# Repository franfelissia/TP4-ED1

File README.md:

# TP4-ED1

Este proyecto contiene el código y los esquemas del trabajo práctico número 4 de Electrónica Digital 1 de la Facultad de Ciencias Exactas, Físicas y Naturales de la Univercidad Nacional de Córdoba hecho por el grupo 15.

## Consigna

Diseñar y construir en protoboard un Conversor de señal analogica a valores digitales (ADC) que realice la conversión de el valor de tensión proveniente de un divisor resistivo variable (potenciómetro) a 8 bits de salida. Los valores para convertir deben ser de 0 a 5 volt, y se supone que tendrán una frecuencia máxima de 2 KHz.

El trabajo consta de tres partes:

1) Adquisición: Realizar la conversión de la señal analógica y mostrar los valores digitales mediante la utilización de leds que muestren si los bits de salida son cero o uno. Para ello se debe seleccionar una de las siguientes 2 opciones:

    - Utilizar un ADC de aproximaciones sucesivas por ejemplo un ADC0808 o ADC0809.
    - Utilizar ADC de la Basys 3 (FPGA)

2) Almacenamiento: Guardar los valores adquiridos en una memoria RAM de 8 bits. Se deberá poder guardar al menos 5 segundos de muestras de la señal de entrada. Posteriormente, se deberá poder ver en los leds los valores almacenados en la memoria.
 
3) Conversión nuevamente a señal análoga (DAC): Convertir los valores digitales a analógico nuevamente, mediante la utilización de un DAC R-2R.
 
Importante:
Para evitar conflictos en el bus de 8 bits que conectará el ADC y la memoria (ambos intentarán controlar el bus), utilizar las salidas alta impedancia de ambos chips. Un switch decidirá si lo que se muestra en los LEDs o en el DAC viene del ADC o de la memoria.

Recomendación: Utilice en la entrada un generador de señales (pañol), seleccione que emita una señal sinusoidal, y vea la salida del R-2R, observando el efecto del muestreo en la forma de onda. Para observar dicho efecto y comparar ambas señales (input y output) puede utilizar un osciloscopio. TENGA EN CUENTA QUE ESTARÁ UTILIZANDO SEÑALES CON PARTE NEGATIVA, POR ENDE, DEBE UTILIZAR EL OFFSET CORRESPONDIENTE DEL GENERADOR DE SEÑALES.
Verificar previamente con el osciloscopio que la señal esté por arriba de 0V.

Componentes:

- RAM estática 32Kx8 bits (1 una)
- Contador de 16 bits con RESET (o 2 chips de 12/14 bits)
- Conversor Digital/Analógico R-2R de 8 bits (1 uno) – Alternativa= Resistencias R-2R y OpAmp

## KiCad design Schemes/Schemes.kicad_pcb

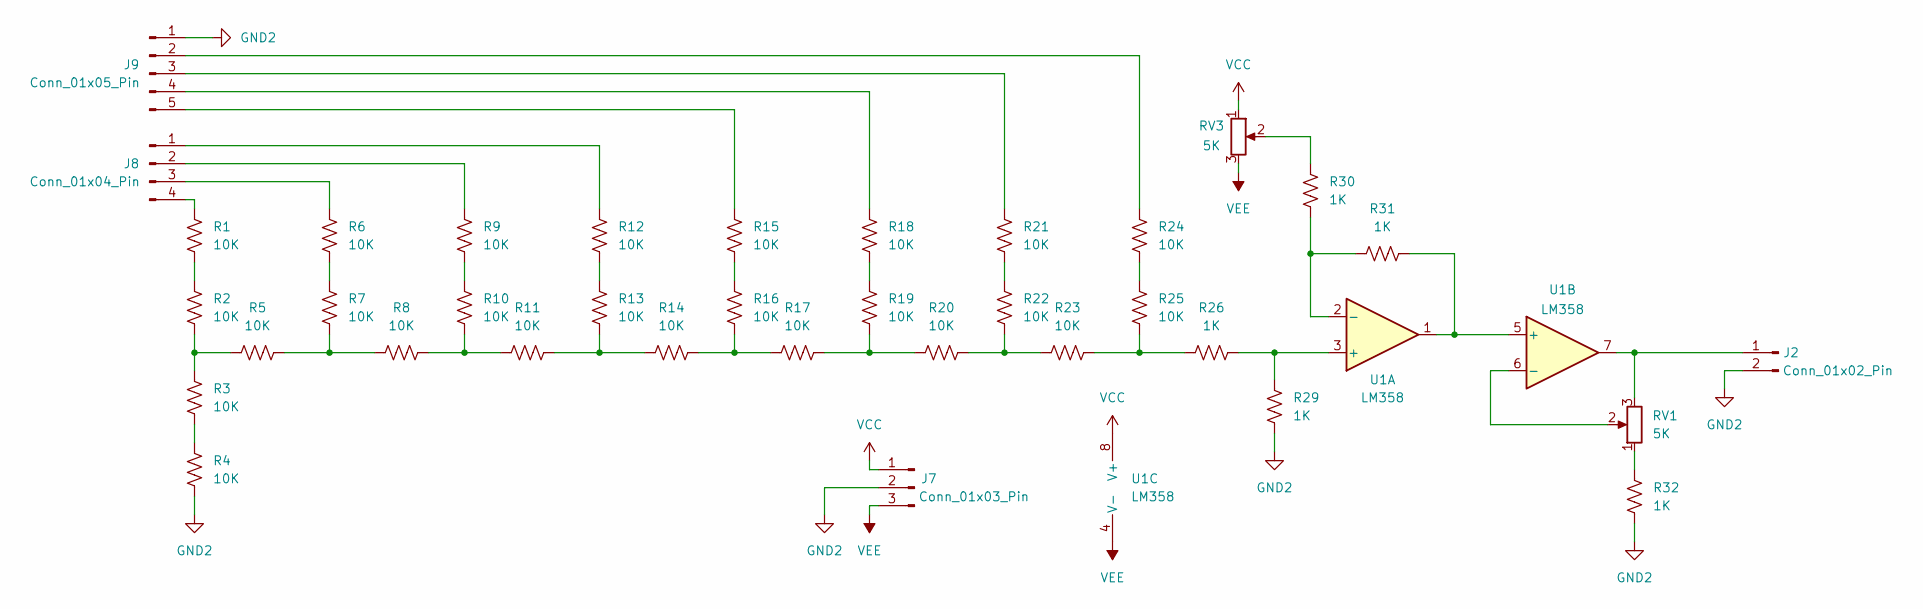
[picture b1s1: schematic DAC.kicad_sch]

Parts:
J2: Conn_01x02_Pin; PinHeader_1x02_P2.54mm_Vertical
J7: Conn_01x03_Pin; TerminalBlock_Phoenix_PT-1,5-3-5.0-H_1x03_P5.00mm_Horizontal
J8: Conn_01x04_Pin; PinHeader_1x04_P2.54mm_Vertical
J9: Conn_01x05_Pin; PinHeader_1x05_P2.54mm_Vertical
R1, R2, R3, R4, R5, R6, R7, R8, R9, R10, R11, R12, R13, R14, R15, R16, R17, R18, R19, R20, R21, R22, R23, R24, R25: 10K; R_Axial_DIN0207_L6.3mm_D2.5mm_P10.16mm_Horizontal
R26, R29, R30, R31, R32: 1K; R_Axial_DIN0207_L6.3mm_D2.5mm_P10.16mm_Horizontal
RV1, RV3: 5K; Potentiometer_Piher_T-16H_Single_Horizontal
U1: LM358; DIP-8_W7.62mm_LongPads

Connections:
GND2: J2.2, J7.2, J9.1, R4.1, R29.1, R32.1
unnamed: J2.1, RV1.3, U1.7
unnamed: J8.1, R12.2
unnamed: J8.2, R9.2
unnamed: J8.3, R6.2
unnamed: J8.4, R1.2
unnamed: J9.2, R24.2
unnamed: J9.3, R21.2
unnamed: J9.4, R18.2
unnamed: J9.5, R15.2
unnamed: R1.1, R2.2
unnamed: R2.1, R3.2, R5.1
unnamed: R3.1, R4.2
unnamed: R5.2, R7.1, R8.1
unnamed: R6.1, R7.2
unnamed: R8.2, R10.1, R11.1
unnamed: R9.1, R10.2
unnamed: R11.2, R13.1, R14.1
unnamed: R12.1, R13.2
unnamed: R14.2, R16.1, R17.1
unnamed: R15.1, R16.2
unnamed: R17.2, R19.1, R20.1
unnamed: R18.1, R19.2
unnamed: R20.2, R22.1, R23.1
unnamed: R21.1, R22.2
unnamed: R23.2, R25.1, R26.2
unnamed: R24.1, R25.2
unnamed: R30.2, RV3.2
unnamed: R32.2, RV1.1
unnamed: R26.1, R29.2, U1.3 (+)
unnamed: R30.1, R31.2, U1.2 (-)
unnamed: R31.1, U1.1, U1.5 (+)
unnamed: RV1.2, U1.6 (-)
VCC: J7.1, RV3.1, U1.8 (V+)
VEE: J7.3, RV3.3, U1.4 (V-)

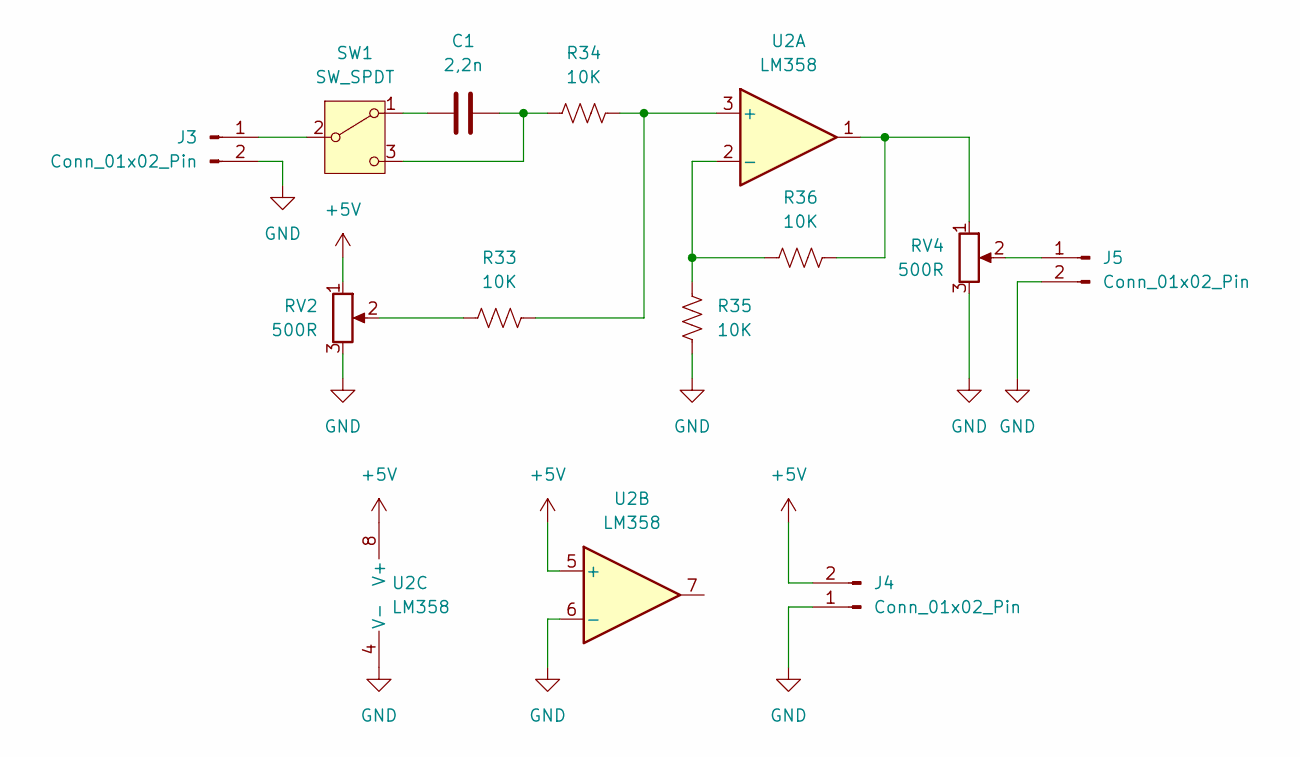
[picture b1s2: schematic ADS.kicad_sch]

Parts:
C1: 2,2n; C_Disc_D7.5mm_W2.5mm_P5.00mm
J3, J5: Conn_01x02_Pin; PinHeader_1x02_P2.54mm_Vertical
J4: Conn_01x02_Pin; TerminalBlock_Phoenix_PT-1,5-2-5.0-H_1x02_P5.00mm_Horizontal
R33, R34, R35, R36: 10K; R_Axial_DIN0207_L6.3mm_D2.5mm_P10.16mm_Horizontal
RV2, RV4: 500R; Potentiometer_Piher_T-16H_Single_Horizontal
SW1: SW_SPDT; Switch
U2: LM358; DIP-8_W7.62mm_LongPads

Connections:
+5V: J4.2, RV2.1, U2.5 (+), U2.8 (V+)
GND: J3.2, J4.1, J5.2, R35.2, RV2.3, RV4.3, U2.4 (V-), U2.6 (-)
unnamed: J3.1, SW1.2 (B)
unnamed: J5.1, RV4.2
unnamed: R33.1, RV2.2
unnamed: R36.2, RV4.1, U2.1
unnamed: C1.1, SW1.1 (A)
unnamed: C1.2, R34.1, SW1.3 (C)
unnamed: R33.2, R34.2, U2.3 (+)
unnamed: R35.1, R36.1, U2.2 (-)

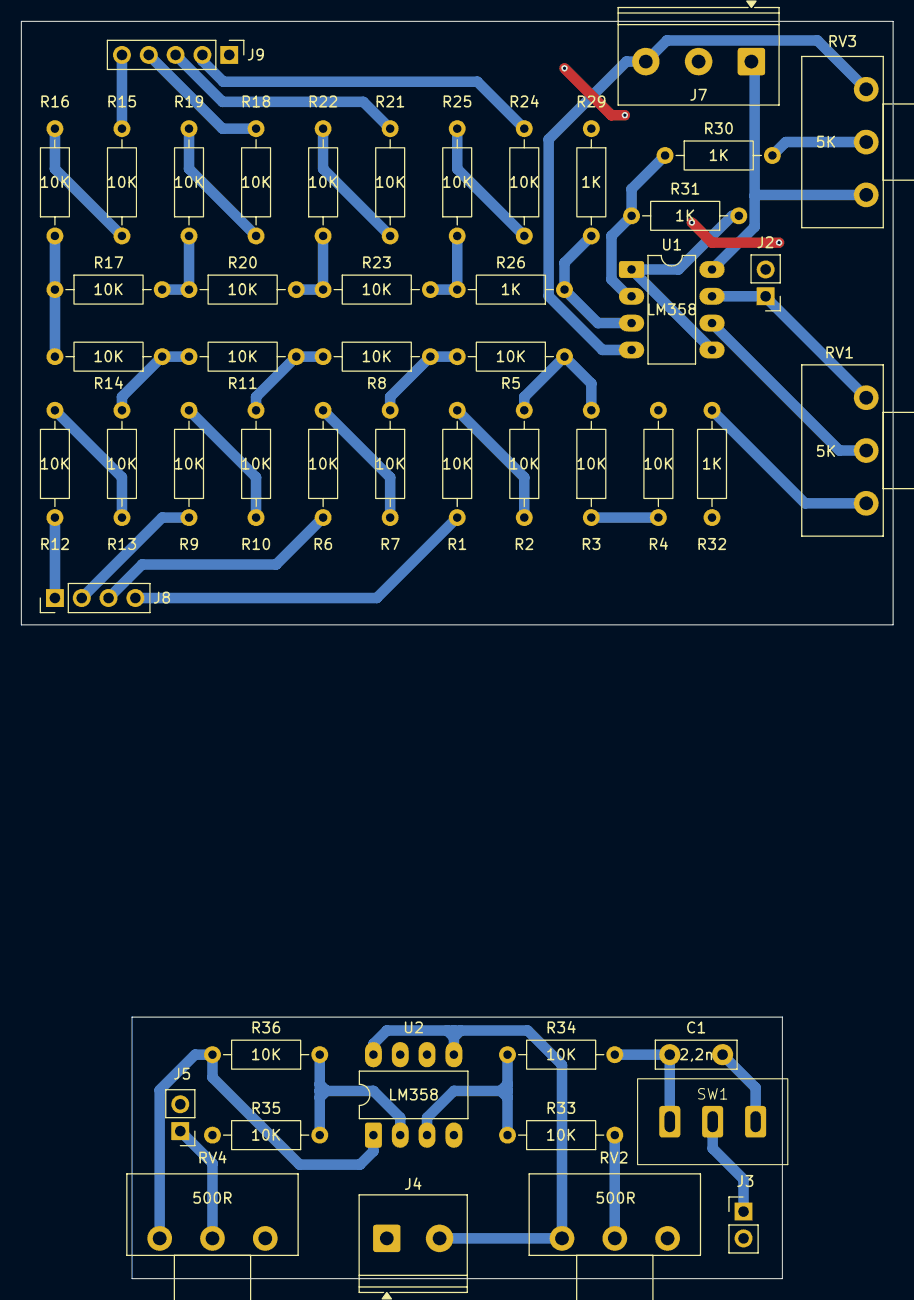
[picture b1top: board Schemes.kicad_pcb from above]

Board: 2 copper layers, 82.5 x 119.1 mm, 49 parts (0 on the bottom side), 45 nets.

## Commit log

2026-06-06 Trabajo Terminado
2026-06-07 Assets Agregados
2026-06-14 TP Mejorado
2026-06-17 Hotfix
